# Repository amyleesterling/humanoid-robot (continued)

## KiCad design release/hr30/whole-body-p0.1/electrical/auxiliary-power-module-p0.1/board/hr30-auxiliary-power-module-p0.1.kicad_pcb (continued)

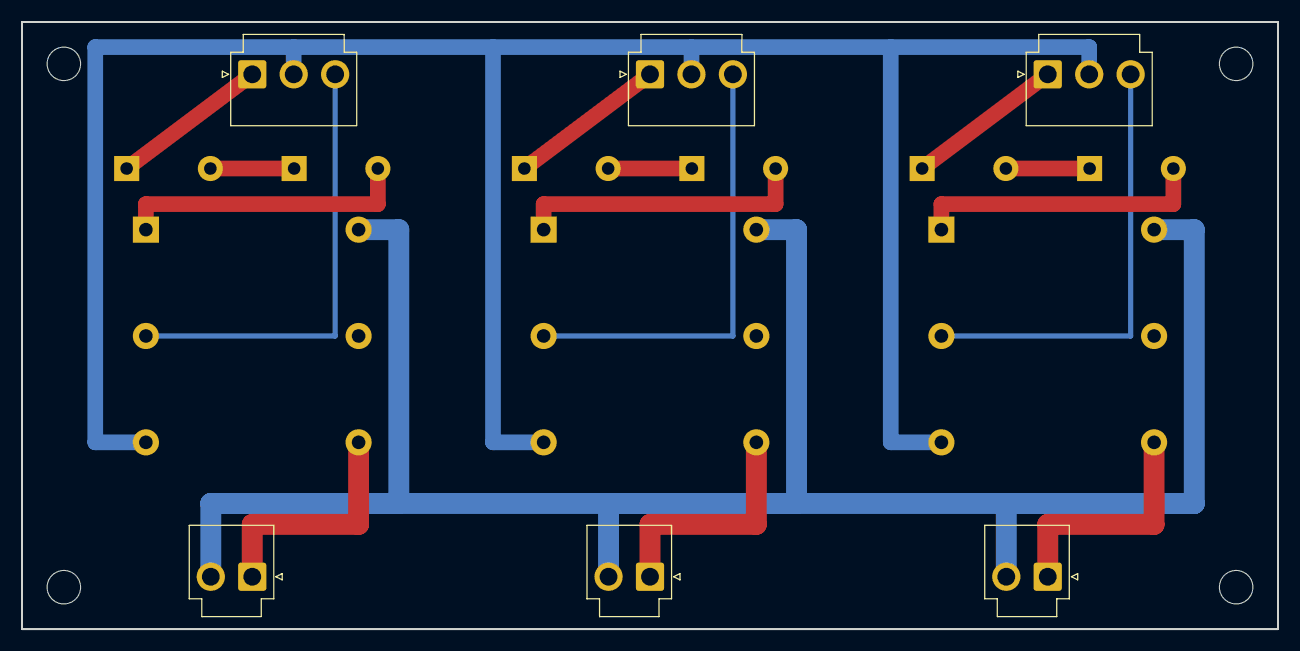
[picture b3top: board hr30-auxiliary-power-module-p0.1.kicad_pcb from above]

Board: 2 copper layers, 120.0 x 58.0 mm, 19 parts (0 on the bottom side), 17 nets.

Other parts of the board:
H1, H2, H3, H4: M3 BOARD MOUNT - STACK/FASTENER SELECTION REQUIRED; MountingHole_3.2mm_M3

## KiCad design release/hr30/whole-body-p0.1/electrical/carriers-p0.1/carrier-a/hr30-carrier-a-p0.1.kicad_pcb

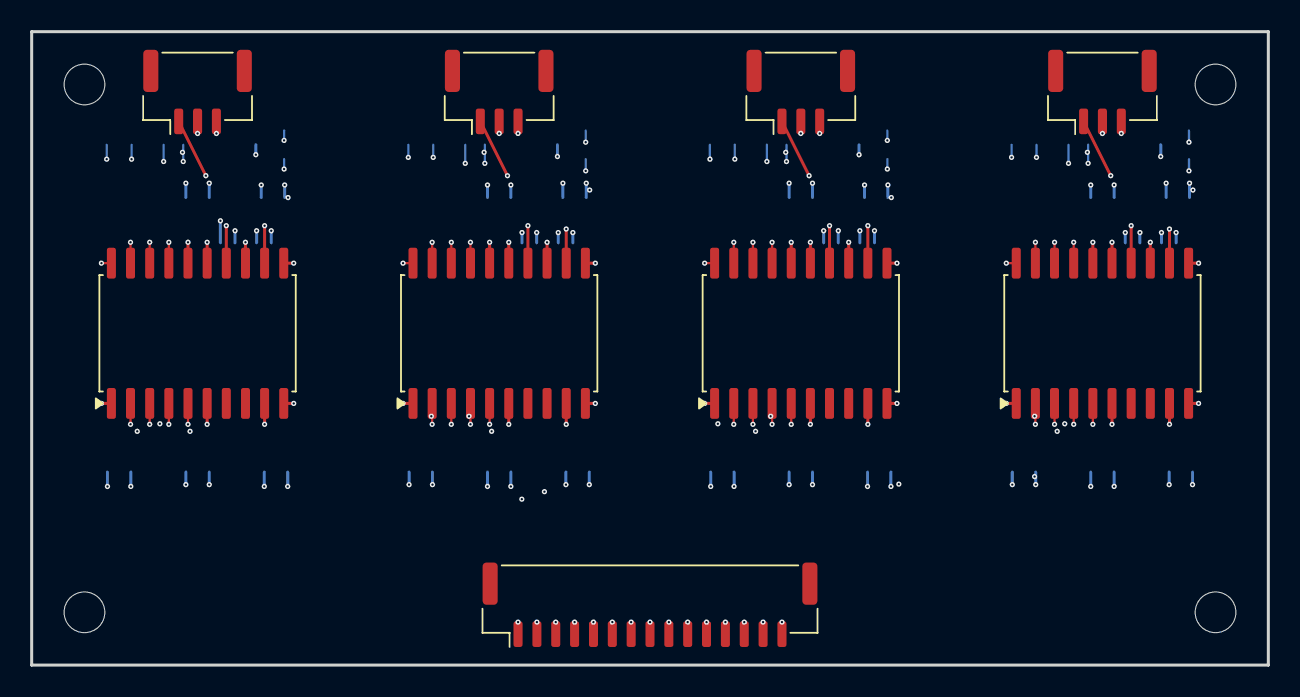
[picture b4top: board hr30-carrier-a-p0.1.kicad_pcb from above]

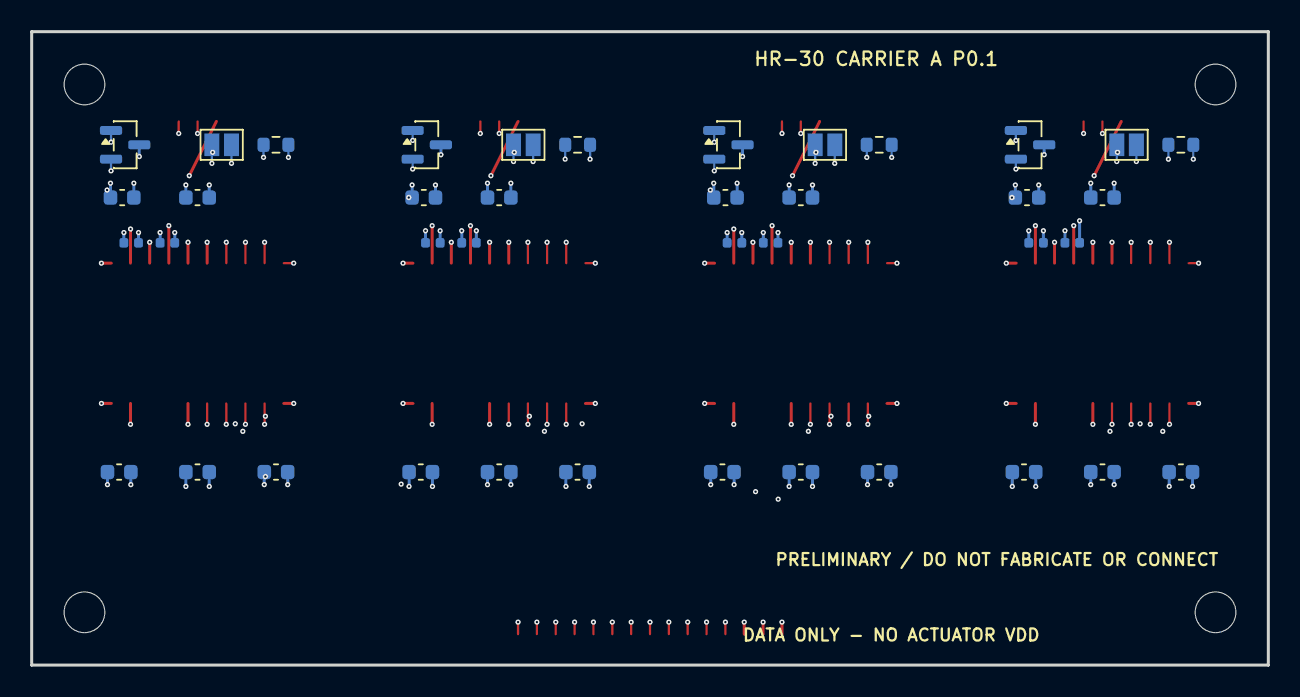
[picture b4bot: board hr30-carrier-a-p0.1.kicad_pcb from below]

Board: 6 copper layers, 82.0 x 42.0 mm, 53 parts (40 on the bottom side), 43 nets.

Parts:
C1A, C2A, C3A, C4A: 10nF 50V X7R; C_0603_1608Metric
C1B, C1D, C2B, C2D, C3B, C3D, C4B, C4D: 10uF 6.3V X5R; C_0603_1608Metric
C1C, C1E, C2C, C2E, C3C, C3E, C4C, C4E: 100nF 50V X7R; C_0603_1608Metric
D1RS, D2RS, D3RS, D4RS: SM712 RS-485 TVS; SOT-23
FB1N, FB2N, FB3N, FB4N: 330R@100MHz isolated return bead; L_0402_1005Metric
FB1P, FB2P, FB3P, FB4P: 330R@100MHz isolated supply bead; L_0402_1005Metric
J101: RS-LLEG data-only field; JST_GH_BM03B-GHS-TBT_1x03-1MP_P1.25mm_Vertical
J102: RS-RLEG data-only field; JST_GH_BM03B-GHS-TBT_1x03-1MP_P1.25mm_Vertical
J103: RS-LARM data-only field; JST_GH_BM03B-GHS-TBT_1x03-1MP_P1.25mm_Vertical
J104: RS-RARM data-only field; JST_GH_BM03B-GHS-TBT_1x03-1MP_P1.25mm_Vertical
JCA1: JST BM15B-GHS-TBT controller; JST_GH_BM15B-GHS-TBT_1x15-1MP_P1.25mm_Vertical
MHA1, MHA2, MHA3, MHA4: M2.5 BOARD-ONLY; TRAY STACK VALIDATION OPEN; MountingHole_2.7mm_M2.5
RT1, RT2, RT3, RT4: 120R 1% termination; R_0603_1608Metric
SJ1, SJ2, SJ3, SJ4: termination enable - OPEN; SolderJumper-2_P1.3mm_Open_Pad1.0x1.5mm
U101: ISOW1432DFMR RS-LLEG; SOIC-20W_7.5x12.8mm_P1.27mm
U102: ISOW1432DFMR RS-RLEG; SOIC-20W_7.5x12.8mm_P1.27mm
U103: ISOW1432DFMR RS-LARM; SOIC-20W_7.5x12.8mm_P1.27mm
U104: ISOW1432DFMR RS-RARM; SOIC-20W_7.5x12.8mm_P1.27mm

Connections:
CTRL_3V3: C1C.1, C2C.1, C3C.1, C4C.1, JCA1.3, U101.1, U102.1, U103.1, U104.1
CTRL_5V: C1A.1, C1B.1, C2A.1, C2B.1, C3A.1, C3B.1, C4A.1, C4B.1, JCA1.2, U101.9, U102.9, U103.9, U104.9
CTRL_GND: C1A.2, C1B.2, C1C.2, C2A.2, C2B.2, C2C.2, C3A.2, C3B.2, C3C.2, C4A.2, C4B.2, C4C.2, JCA1.1, U101.6, U101.10, U102.6, U102.10, U103.6, U103.10, U104.6, U104.10
RS-LARM_DN: D3RS.2, J103.3, SJ3.2, U103.18, U103.19
RS-LARM_DP: D3RS.1, J103.2, RT3.1, U103.17, U103.20
RS-LARM_GND2: C3D.2, FB3N.1, U103.11, U103.13
RS-LARM_RET: C3E.2, D3RS.3, FB3N.2, J103.1, U103.14, U103.15
RS-LARM_TERM: RT3.2, SJ3.1
RS-LARM_VISOIN: C3E.1, FB3P.2, U103.16
RS-LARM_VISOOUT: C3D.1, FB3P.1, U103.12
RS-LLEG_DN: D1RS.2, J101.3, SJ1.2, U101.18, U101.19
RS-LLEG_DP: D1RS.1, J101.2, RT1.1, U101.17, U101.20
RS-LLEG_GND2: C1D.2, FB1N.1, U101.11, U101.13
RS-LLEG_RET: C1E.2, D1RS.3, FB1N.2, J101.1, U101.14, U101.15
RS-LLEG_TERM: RT1.2, SJ1.1
RS-LLEG_VISOIN: C1E.1, FB1P.2, U101.16
RS-LLEG_VISOOUT: C1D.1, FB1P.1, U101.12
RS-RARM_DN: D4RS.2, J104.3, SJ4.2, U104.18, U104.19
RS-RARM_DP: D4RS.1, J104.2, RT4.1, U104.17, U104.20
RS-RARM_GND2: C4D.2, FB4N.1, U104.11, U104.13
RS-RARM_RET: C4E.2, D4RS.3, FB4N.2, J104.1, U104.14, U104.15
RS-RARM_TERM: RT4.2, SJ4.1
RS-RARM_VISOIN: C4E.1, FB4P.2, U104.16
RS-RARM_VISOOUT: C4D.1, FB4P.1, U104.12
RS-RLEG_DN: D2RS.2, J102.3, SJ2.2, U102.18, U102.19
RS-RLEG_DP: D2RS.1, J102.2, RT2.1, U102.17, U102.20
RS-RLEG_GND2: C2D.2, FB2N.1, U102.11, U102.13
RS-RLEG_RET: C2E.2, D2RS.3, FB2N.2, J102.1, U102.14, U102.15
RS-RLEG_TERM: RT2.2, SJ2.1
RS-RLEG_VISOIN: C2E.1, FB2P.2, U102.16
RS-RLEG_VISOOUT: C2D.1, FB2P.1, U102.12
UART_RS-LARM_DIR: JCA1.12, U103.3, U103.5
UART_RS-LARM_RX: JCA1.11, U103.4
UART_RS-LARM_TX: JCA1.10, U103.2
UART_RS-LLEG_DIR: JCA1.6, U101.3, U101.5
UART_RS-LLEG_RX: JCA1.5, U101.4
UART_RS-LLEG_TX: JCA1.4, U101.2
UART_RS-RARM_DIR: JCA1.15, U104.3, U104.5
UART_RS-RARM_RX: JCA1.14, U104.4
UART_RS-RARM_TX: JCA1.13, U104.2
UART_RS-RLEG_DIR: JCA1.9, U102.3, U102.5
UART_RS-RLEG_RX: JCA1.8, U102.4
UART_RS-RLEG_TX: JCA1.7, U102.2

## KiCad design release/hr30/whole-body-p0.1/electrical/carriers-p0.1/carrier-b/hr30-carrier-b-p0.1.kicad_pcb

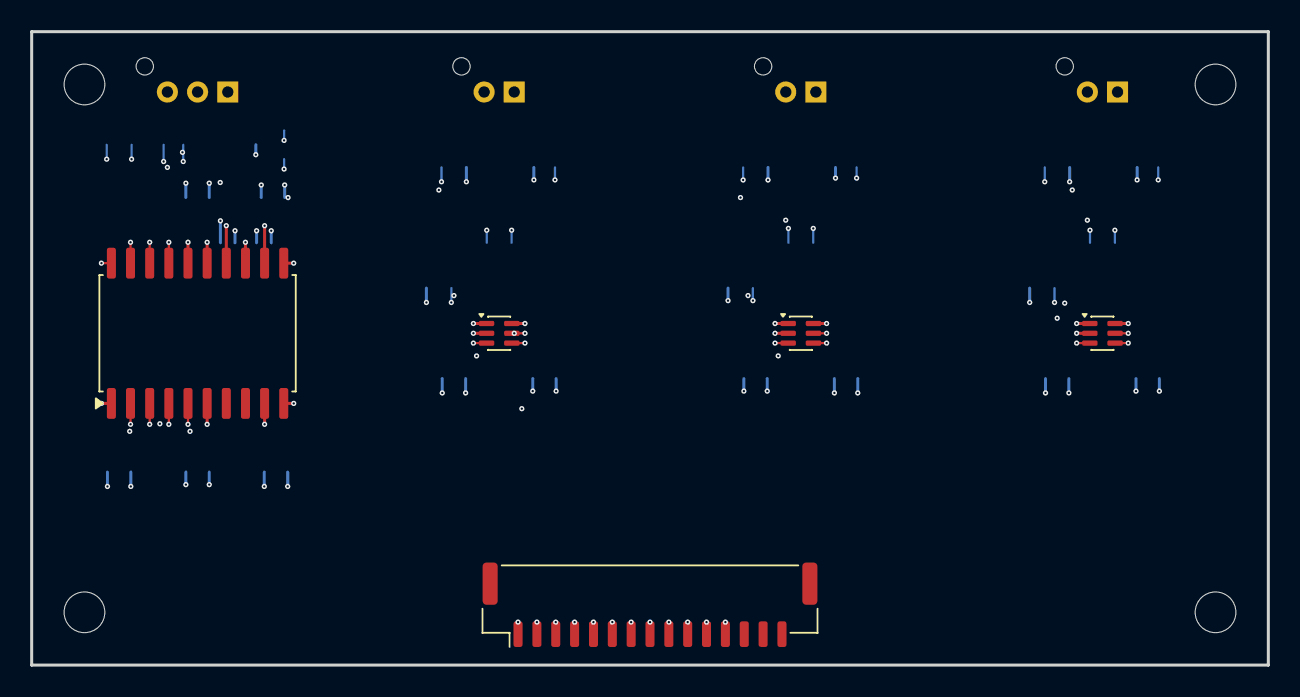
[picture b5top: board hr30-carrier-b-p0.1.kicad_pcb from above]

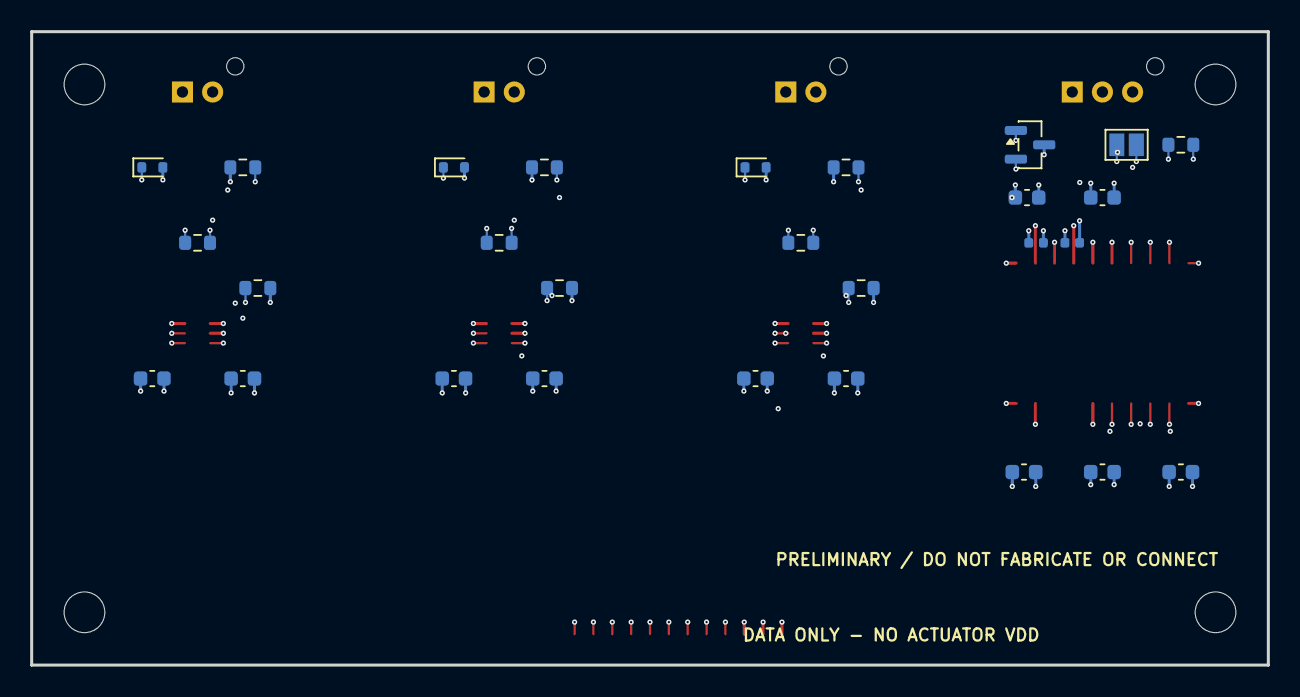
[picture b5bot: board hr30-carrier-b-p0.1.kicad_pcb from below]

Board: 6 copper layers, 82.0 x 42.0 mm, 41 parts (28 on the bottom side), 25 nets.

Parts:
C5A: 10nF 50V X7R; C_0603_1608Metric
C5B, C5D: 10uF 6.3V X5R; C_0603_1608Metric
C5C, C5E: 100nF 50V X7R; C_0603_1608Metric
C201A, C202A, C203A: 100nF 50V X7R VCCA; C_0603_1608Metric
C201B, C202B, C203B: 100nF 50V X7R VCCB; C_0603_1608Metric
D5RS: SM712 RS-485 TVS; SOT-23
D201, D202, D203: TPD1E10B06 TTL ESD; D_SOD-523
FB5N: 330R@100MHz isolated return bead; L_0402_1005Metric
FB5P: 330R@100MHz isolated supply bead; L_0402_1005Metric
J105: RS-WAIST data-only field; JST_PA_B03B-PASK-1
J201: TTL-LDIST data-only field; JST_PA_B02B-PASK-1
J202: TTL-RDIST data-only field; JST_PA_B02B-PASK-1
J203: TTL-HEAD data-only field; JST_PA_B02B-PASK-1
JCB1: JST BM15B-GHS-TBT controller; JST_GH_BM15B-GHS-TBT_1x15-1MP_P1.25mm_Vertical
MHB1, MHB2, MHB3, MHB4: M2.5 BOARD-ONLY; TRAY STACK VALIDATION OPEN; MountingHole_2.7mm_M2.5
R201D, R202D, R203D: 100k 1% DIR pulldown; R_0603_1608Metric
R201P, R202P, R203P: 10k idle pullup - DNP; R_0603_1608Metric
R201S, R202S, R203S: 33R 1% series; R_0603_1608Metric
RT5: 120R 1% termination; R_0603_1608Metric
SJ5: termination enable - OPEN; SolderJumper-2_P1.3mm_Open_Pad1.0x1.5mm
U105: ISOW1432DFMR RS-WAIST; SOIC-20W_7.5x12.8mm_P1.27mm
U201: SN74LVC1T45DCKR TTL-LDIST; SOT-363_SC-70-6
U202: SN74LVC1T45DCKR TTL-RDIST; SOT-363_SC-70-6
U203: SN74LVC1T45DCKR TTL-HEAD; SOT-363_SC-70-6

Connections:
CTRL_3V3: C5C.1, C201A.1, C202A.1, C203A.1, JCB1.3, U105.1, U201.1, U202.1, U203.1
CTRL_5V: C5A.1, C5B.1, C201B.1, C202B.1, C203B.1, JCB1.2, R201P.1, R202P.1, R203P.1, U105.9, U201.6, U202.6, U203.6
CTRL_GND: C5A.2, C5B.2, C5C.2, C201A.2, C201B.2, C202A.2, C202B.2, C203A.2, C203B.2, D201.2, D202.2, D203.2, J201.1, J202.1, J203.1, JCB1.1, R201D.2, R202D.2, R203D.2, U105.6, U105.10, U201.2, U202.2, U203.2
RS-WAIST_DN: D5RS.2, J105.3, SJ5.2, U105.18, U105.19
RS-WAIST_DP: D5RS.1, J105.2, RT5.1, U105.17, U105.20
RS-WAIST_GND2: C5D.2, FB5N.1, U105.11, U105.13
RS-WAIST_RET: C5E.2, D5RS.3, FB5N.2, J105.1, U105.14, U105.15
RS-WAIST_TERM: RT5.2, SJ5.1
RS-WAIST_VISOIN: C5E.1, FB5P.2, U105.16
RS-WAIST_VISOOUT: C5D.1, FB5P.1, U105.12
TTL-HEAD_DATA: D203.1, J203.2, R203P.2, R203S.2
TTL-HEAD_DATA_PRE: R203S.1, U203.4
TTL-LDIST_DATA: D201.1, J201.2, R201P.2, R201S.2
TTL-LDIST_DATA_PRE: R201S.1, U201.4
TTL-RDIST_DATA: D202.1, J202.2, R202P.2, R202S.2
TTL-RDIST_DATA_PRE: R202S.1, U202.4
UART_RS-WAIST_DIR: JCB1.6, U105.3, U105.5
UART_RS-WAIST_RX: JCB1.5, U105.4
UART_RS-WAIST_TX: JCB1.4, U105.2
UART_TTL-HEAD_DIR: JCB1.12, R203D.1, U203.5
UART_TTL-HEAD_TX: JCB1.11, U203.3
UART_TTL-LDIST_DIR: JCB1.8, R201D.1, U201.5
UART_TTL-LDIST_TX: JCB1.7, U201.3
UART_TTL-RDIST_DIR: JCB1.10, R202D.1, U202.5
UART_TTL-RDIST_TX: JCB1.9, U202.3

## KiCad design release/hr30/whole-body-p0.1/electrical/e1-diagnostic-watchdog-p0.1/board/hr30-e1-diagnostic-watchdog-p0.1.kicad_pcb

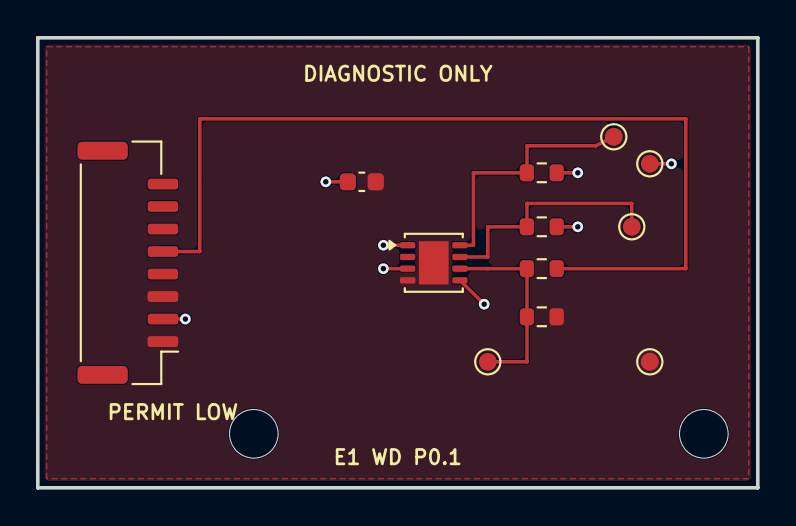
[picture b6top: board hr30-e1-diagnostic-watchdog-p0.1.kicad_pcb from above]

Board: 2 copper layers, 40.0 x 25.0 mm, 14 parts (0 on the bottom side), 6 nets.

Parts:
C1: SELECTION REQUIRED; C_0603_1608Metric
H1, H2: M2.5 FIXTURE HOLE; MountingHole_2.7mm_M2.5
J1: BM08B-GHS-TBT; JST_GH_BM08B-GHS-TBT_1x08-1MP_P1.25mm_Vertical
R1, R2, R5, R6: SELECTION REQUIRED; R_0603_1608Metric
TP1, TP2, TP3, TP4, TP5: N/A; TestPoint_Pad_D1.0mm
U1: TPS3431SDRBR; VSON-8-1EP_3x3mm_P0.65mm_EP1.65x2.4mm

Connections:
CTRL_3V3: C1.1, J1.2, R5.1, R6.1, TP4.1, U1.1, U1.3, U1.5
CTRL_GND: C1.2, J1.1, J1.3, R2.2, TP5.1, U1.4, U1.9
MOTION_WD_HEARTBEAT: J1.5, R1.1
WD_ENOUT: R6.2, TP3.1, U1.8
WD_INPUT: R1.2, R2.1, TP1.1, U1.6
WD_OUTPUT_N: R5.2, TP2.1, U1.7

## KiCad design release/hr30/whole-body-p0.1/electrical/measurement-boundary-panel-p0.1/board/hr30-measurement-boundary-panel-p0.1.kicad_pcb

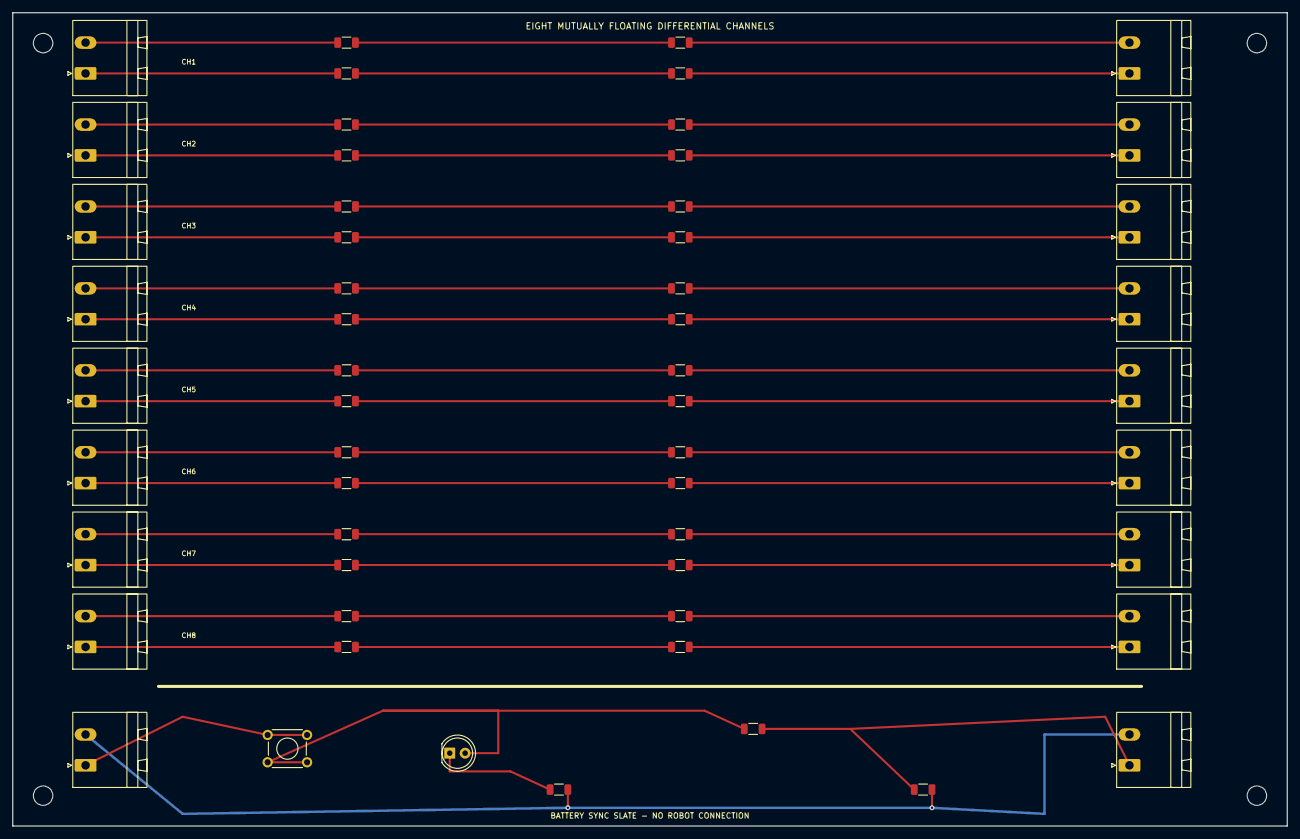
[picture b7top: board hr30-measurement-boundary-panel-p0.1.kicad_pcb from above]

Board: 2 copper layers, 210.0 x 134.0 mm, 59 parts (0 on the bottom side), 53 nets.

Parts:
D1: WP7113QBC/D; LED_D5.0mm_Clear
H1, H2, H3, H4: M3 ENCLOSURE STANDOFF; MountingHole_3.2mm_M3
J1I, J1O, J2I, J2O, J3I, J3O, J4I, J4O, J5I, J5O, J6I, J6O, J7I, J7O, J8I, J8O: 1757242; PhoenixContact_MSTBA_2,5_2-G-5,08_1x02_P5.08mm_Horizontal
JBT1: 1757242; PhoenixContact_MSTBA_2,5_2-G-5,08_1x02_P5.08mm_Horizontal
JTTL: 1757242; PhoenixContact_MSTBA_2,5_2-G-5,08_1x02_P5.08mm_Horizontal
R1A, R1B, R1C, R1D, R2A, R2B, R2C, R2D, R3A, R3B, R3C, R3D, R4A, R4B, R4C, R4D, R5A, R5B, R5C, R5D, R6A, R6B, R6C, R6D, R7A, R7B, R7C, R7D, R8A, R8B, R8C, R8D: TNPW12065K10BEEA; R_1206_3216Metric
RSL1: TNPW1206330RBEEA; R_1206_3216Metric
RSL2: TNPW12061K00BEEA; R_1206_3216Metric
RSL3: TNPW1206100KBEEA; R_1206_3216Metric
SW1: B3F-1000; SW_TH_Tactile_Omron_B3F-100x

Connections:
CH1_HI_IN: J1I.1, R1A.1
CH1_HI_MID: R1A.2, R1B.1
CH1_HI_OUT: J1O.1, R1B.2
CH1_LO_IN: J1I.2, R1C.1
CH1_LO_MID: R1C.2, R1D.1
CH1_LO_OUT: J1O.2, R1D.2
CH2_HI_IN: J2I.1, R2A.1
CH2_HI_MID: R2A.2, R2B.1
CH2_HI_OUT: J2O.1, R2B.2
CH2_LO_IN: J2I.2, R2C.1
CH2_LO_MID: R2C.2, R2D.1
CH2_LO_OUT: J2O.2, R2D.2
CH3_HI_IN: J3I.1, R3A.1
CH3_HI_MID: R3A.2, R3B.1
CH3_HI_OUT: J3O.1, R3B.2
CH3_LO_IN: J3I.2, R3C.1
CH3_LO_MID: R3C.2, R3D.1
CH3_LO_OUT: J3O.2, R3D.2
CH4_HI_IN: J4I.1, R4A.1
CH4_HI_MID: R4A.2, R4B.1
CH4_HI_OUT: J4O.1, R4B.2
CH4_LO_IN: J4I.2, R4C.1
CH4_LO_MID: R4C.2, R4D.1
CH4_LO_OUT: J4O.2, R4D.2
CH5_HI_IN: J5I.1, R5A.1
CH5_HI_MID: R5A.2, R5B.1
CH5_HI_OUT: J5O.1, R5B.2
CH5_LO_IN: J5I.2, R5C.1
CH5_LO_MID: R5C.2, R5D.1
CH5_LO_OUT: J5O.2, R5D.2
CH6_HI_IN: J6I.1, R6A.1
CH6_HI_MID: R6A.2, R6B.1
CH6_HI_OUT: J6O.1, R6B.2
CH6_LO_IN: J6I.2, R6C.1
CH6_LO_MID: R6C.2, R6D.1
CH6_LO_OUT: J6O.2, R6D.2
CH7_HI_IN: J7I.1, R7A.1
CH7_HI_MID: R7A.2, R7B.1
CH7_HI_OUT: J7O.1, R7B.2
CH7_LO_IN: J7I.2, R7C.1
CH7_LO_MID: R7C.2, R7D.1
CH7_LO_OUT: J7O.2, R7D.2
CH8_HI_IN: J8I.1, R8A.1
CH8_HI_MID: R8A.2, R8B.1
CH8_HI_OUT: J8O.1, R8B.2
CH8_LO_IN: J8I.2, R8C.1
CH8_LO_MID: R8C.2, R8D.1
CH8_LO_OUT: J8O.2, R8D.2
SLATE_ACTIVE: D1.2, RSL2.1, SW1.2
SLATE_BAT_POS: JBT1.1, SW1.1
SLATE_BAT_RET: JBT1.2, JTTL.2, RSL1.2, RSL3.2
SLATE_LED_RET: D1.1, RSL1.1
SLATE_OUT: JTTL.1, RSL2.2, RSL3.1

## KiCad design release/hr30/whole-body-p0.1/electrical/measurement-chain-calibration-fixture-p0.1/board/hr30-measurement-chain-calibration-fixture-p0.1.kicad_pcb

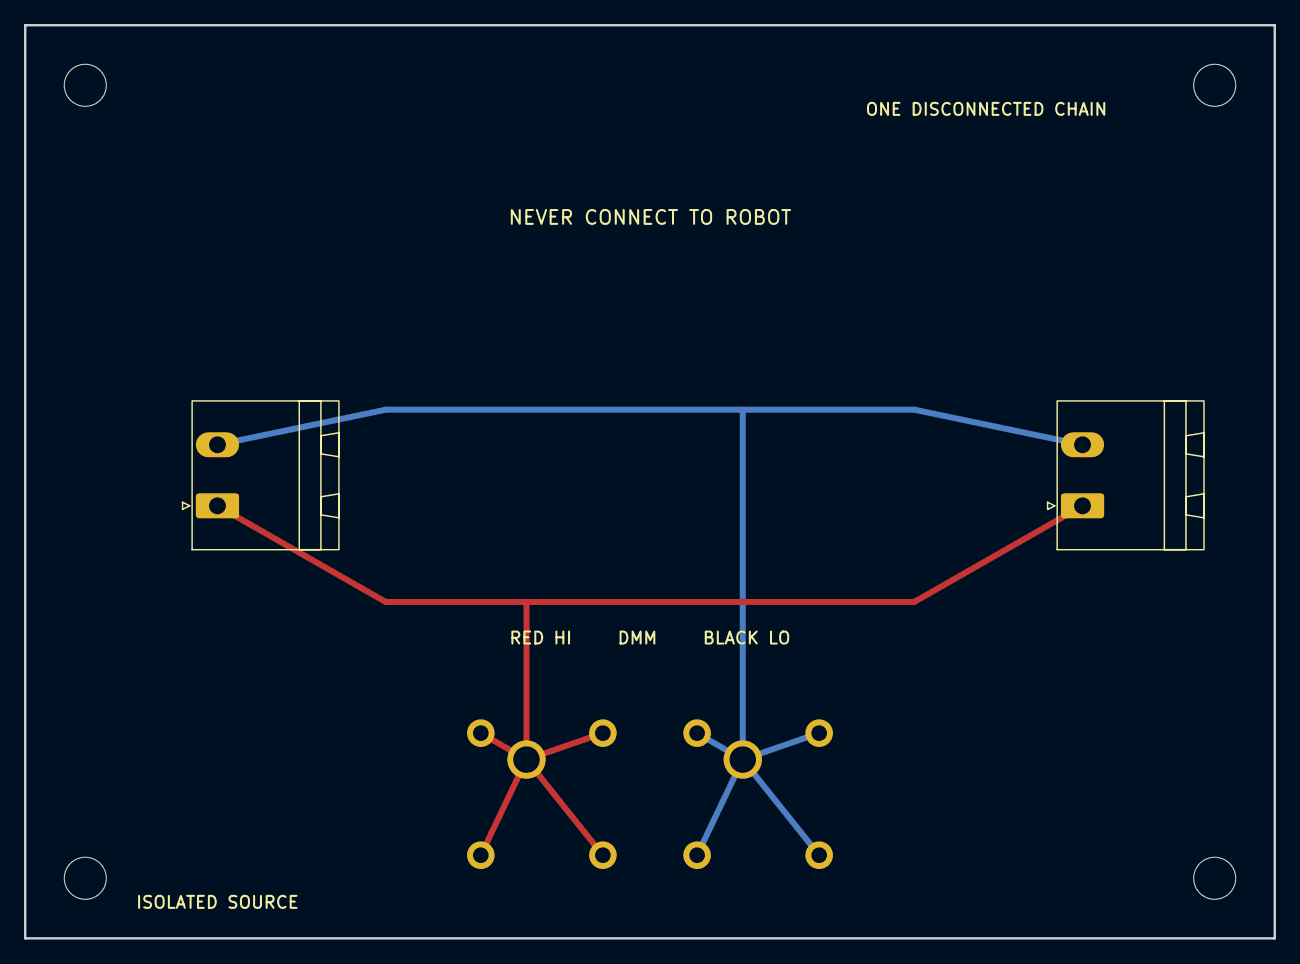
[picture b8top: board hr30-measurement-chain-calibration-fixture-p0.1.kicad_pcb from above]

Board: 2 copper layers, 104.0 x 76.0 mm, 8 parts (0 on the bottom side), 2 nets.

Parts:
H1, H2, H3, H4: ENCLOSURE STANDOFF FAI REQUIRED; MountingHole_3.5mm
JDUT: 1757242; PhoenixContact_MSTBA_2,5_2-G-5,08_1x02_P5.08mm_Horizontal
JHI: 73099-2 RED; POMONA_73099
JLO: 73099-0 BLACK; POMONA_73099
JPS: 1757242; PhoenixContact_MSTBA_2,5_2-G-5,08_1x02_P5.08mm_Horizontal

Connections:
CAL_HI: JDUT.1, JHI.1, JPS.1
CAL_LO: JDUT.2, JLO.1, JPS.2
